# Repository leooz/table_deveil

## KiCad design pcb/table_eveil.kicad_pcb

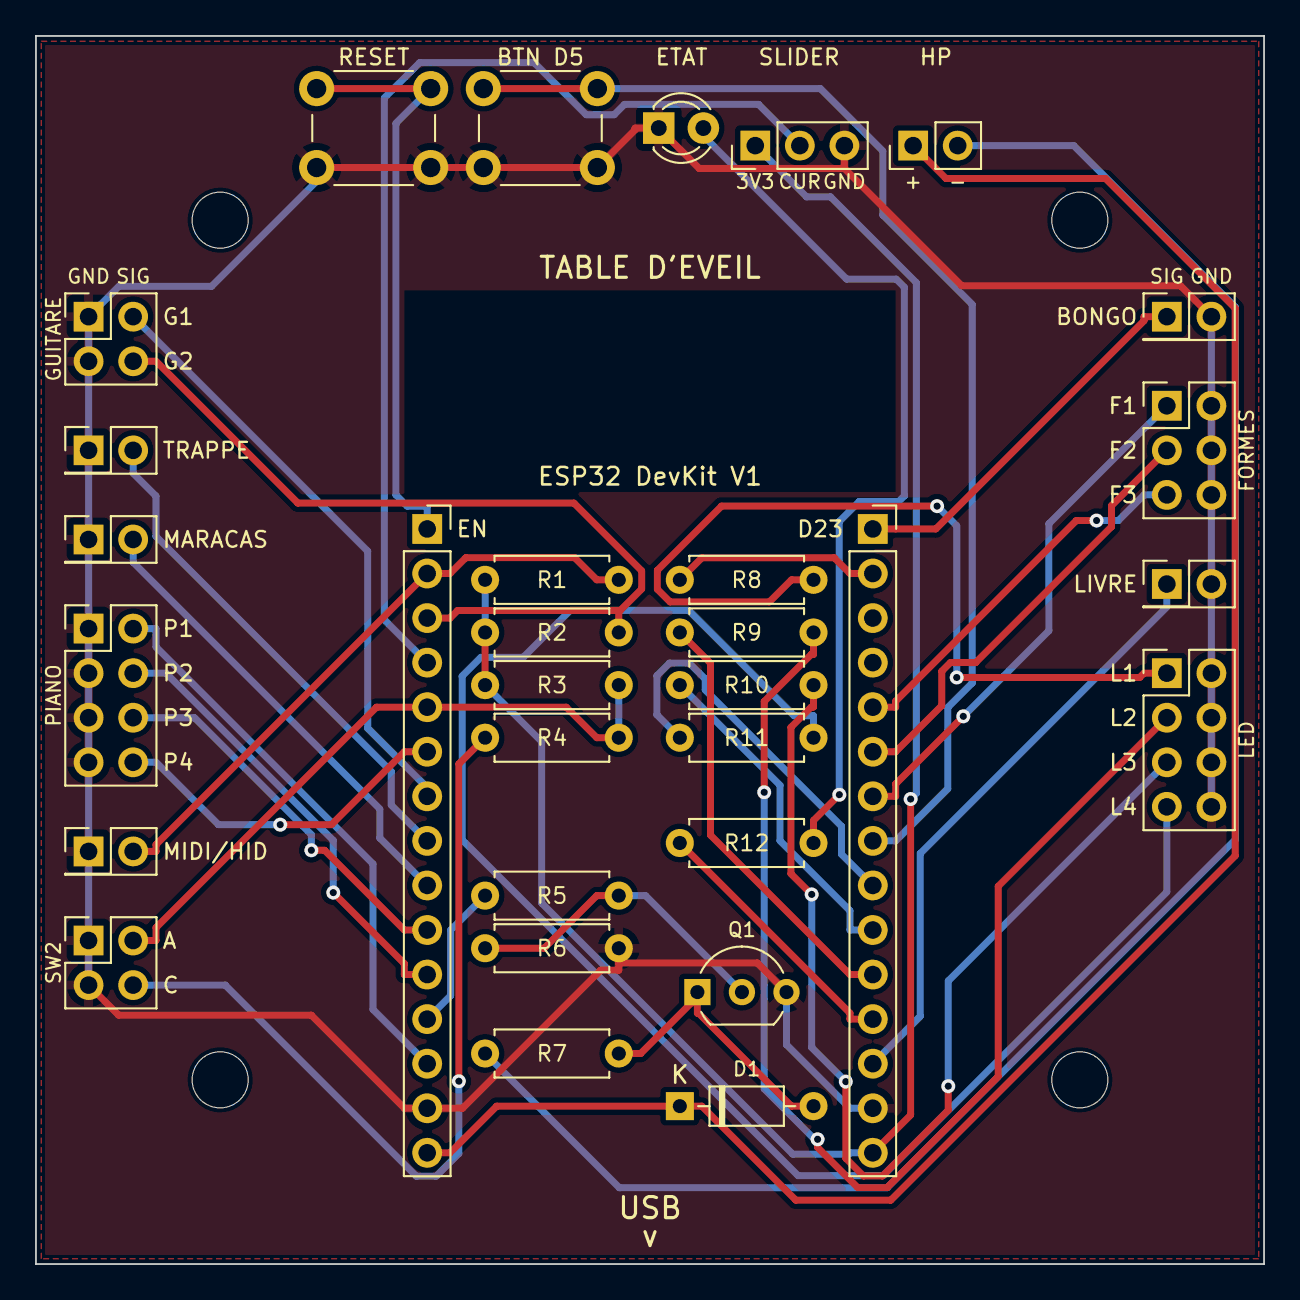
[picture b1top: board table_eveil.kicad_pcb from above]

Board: 2 copper layers, 70.0 x 70.0 mm, 35 parts (0 on the bottom side), 36 nets.

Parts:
D1: 1N4148; D_DO-35_SOD27_P7.62mm_Horizontal
D2: LED etat; LED_D3.0mm
H1, H2, H3, H4: M3; MountingHole_3.2mm_M3
J1: GUITARE; PinHeader_2x02_P2.54mm_Vertical
J2: TRAPPE; PinHeader_2x01_P2.54mm_Vertical
J3: MARACAS; PinHeader_2x01_P2.54mm_Vertical
J4: PIANO; PinHeader_2x04_P2.54mm_Vertical
J5: SW1; PinHeader_2x01_P2.54mm_Vertical
J6: SW2; PinHeader_2x02_P2.54mm_Vertical
J7: BONGO; PinHeader_2x01_P2.54mm_Vertical
J8: FORMES; PinHeader_2x03_P2.54mm_Vertical
J9: LIVRE; PinHeader_2x01_P2.54mm_Vertical
J10: LED; PinHeader_2x04_P2.54mm_Vertical
J11: SLIDER; PinHeader_1x03_P2.54mm_Vertical
J12: HAUT-PARLEUR; PinHeader_1x02_P2.54mm_Vertical
Q1: BC337; TO-92_Inline_Wide
R1, R2, R3, R4, R6: 10k; R_Axial_DIN0207_L6.3mm_D2.5mm_P7.62mm_Horizontal
R5, R12: 1k; R_Axial_DIN0207_L6.3mm_D2.5mm_P7.62mm_Horizontal
R7: 47R 0.5W; R_Axial_DIN0207_L6.3mm_D2.5mm_P7.62mm_Horizontal
R8, R9, R10, R11: 220R; R_Axial_DIN0207_L6.3mm_D2.5mm_P7.62mm_Horizontal
SW1: RESET; SW_PUSH_6mm
SW2: BOUTON; SW_PUSH_6mm
U1A: DevKit gauche; PinSocket_1x15_P2.54mm_Vertical
U1B: DevKit droite; PinSocket_1x15_P2.54mm_Vertical

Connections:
+3V3: J11.1, R1.1, R2.1, R3.1, U1B.15
+5V: D1.1, J12.1, U1A.15
EN: SW1.1, U1A.1
GND: D2.1, J1.1, J1.3, J2.1, J3.1, J4.1, J4.3, J4.5, J4.7, J5.1, J6.1, J6.3, J7.2, J8.2, J8.4, J8.6, J9.2, J10.2, J10.4, J10.6, J10.8, J11.3, Q1.3, R6.2, SW1.2, SW2.2, U1A.14, U1B.14
IO2: R12.1, U1B.12
IO4: R9.1, U1B.11
IO5: SW2.1, U1B.8
IO12: R5.1, U1A.12
IO13: J4.2, U1A.13
IO14: J4.4, U1A.11
IO15: J9.1, U1B.13
IO16: R10.1, U1B.10
IO17: R11.1, U1B.9
IO18: J8.1, U1B.7
IO19: J8.3, U1B.6
IO21: J8.5, U1B.5
IO22: R8.1, U1B.2
IO23: J7.1, U1B.1
IO25: J2.2, U1A.8
IO26: J3.2, U1A.9
IO27: J4.6, U1A.10
IO32: J4.8, U1A.6
IO33: J1.2, U1A.7
IO34: J11.2, U1A.4
IO35: J6.2, R3.2, R4.2, U1A.5
LED1: J10.1, R8.2
LED2: J10.3, R9.2
LED3: J10.5, R10.2
LED4: J10.7, R11.2
LED_ST: D2.2, R12.2
Q_B: Q1.2, R5.2, R6.1
Q_C: D1.2, Q1.1, R7.2
SPK_N: J12.2, R7.1
SW2_C: J6.4, R4.1
VN39: J1.4, R2.2, U1A.3
VP36: J5.2, R1.2, U1A.2
